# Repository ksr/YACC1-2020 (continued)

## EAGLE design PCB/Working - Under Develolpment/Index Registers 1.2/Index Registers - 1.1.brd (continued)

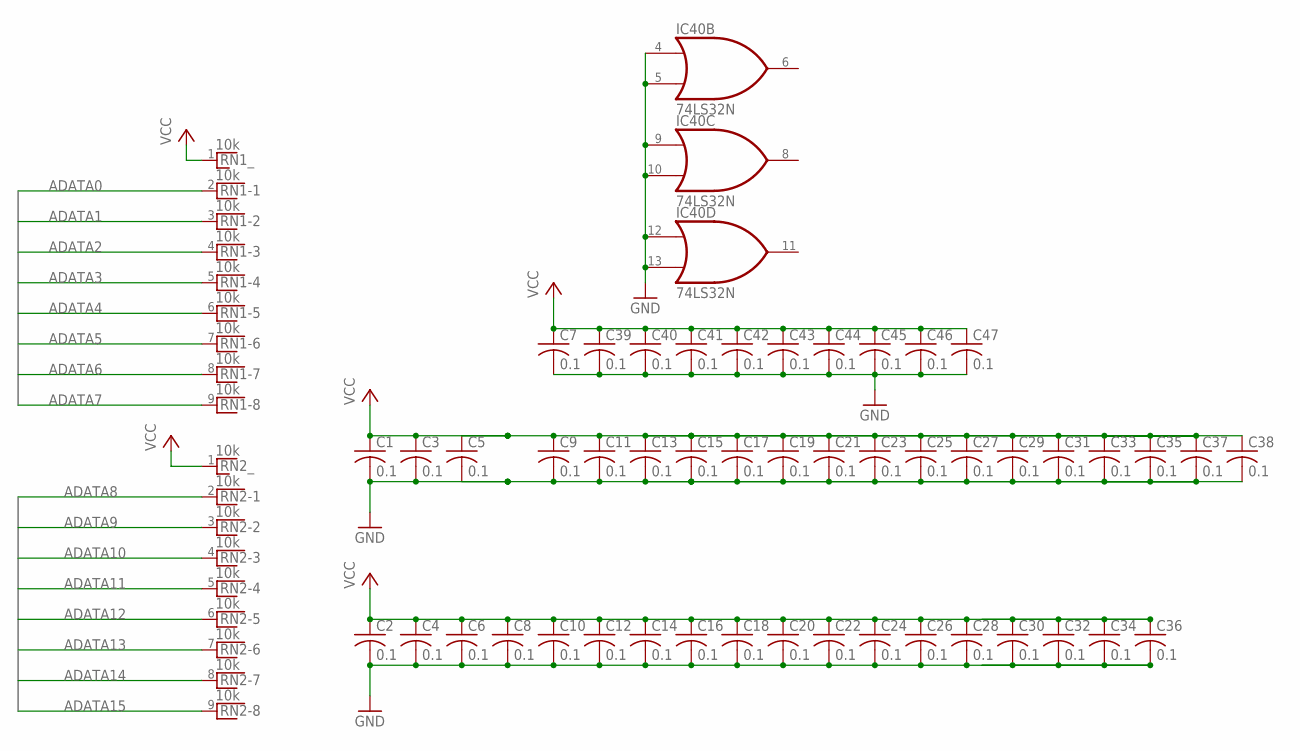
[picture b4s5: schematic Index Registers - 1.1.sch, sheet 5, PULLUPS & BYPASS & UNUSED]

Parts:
C1, C2, C3, C4, C5, C6, C7, C8, C9, C10, C11, C12, C13, C14, C15, C16, C17, C18, C19, C20, C21, C22, C23, C24, C25, C26, C27, C28, C29, C30, C31, C32, C33, C34, C35, C36, C37, C38, C39, C40, C41, C42, C43, C44, C45, C46, C47: 0.1; C025-040X050
IC40: 74LS32N; DIL14
RN1, RN2: 10k; RN-9

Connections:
ADATA0: RN1.2; also elsewhere on the board
ADATA1: RN1.3; also elsewhere on the board
ADATA2: RN1.4; also elsewhere on the board
ADATA3: RN1.5; also elsewhere on the board
ADATA4: RN1.6; also elsewhere on the board
ADATA5: RN1.7; also elsewhere on the board
ADATA6: RN1.8; also elsewhere on the board
ADATA7: RN1.9; also elsewhere on the board
ADATA8: RN2.2; also elsewhere on the board
ADATA9: RN2.3; also elsewhere on the board
ADATA10: RN2.4; also elsewhere on the board
ADATA11: RN2.5; also elsewhere on the board
ADATA12: RN2.6; also elsewhere on the board
ADATA13: RN2.7; also elsewhere on the board
ADATA14: RN2.8; also elsewhere on the board
ADATA15: RN2.9; also elsewhere on the board
GND: C1.2, C2.2, C3.2, C4.2, C5.2, C6.2, C7.2, C8.2, C9.2, C10.2, C11.2, C12.2, C13.2, C14.2, C15.2, C16.2, C17.2, C18.2, C19.2, C20.2, C21.2, C22.2, C23.2, C24.2, C25.2, C26.2, C27.2, C28.2, C29.2, C30.2, C31.2, C32.2, C33.2, C34.2, C35.2, C36.2, C37.2, C38.2, C39.2, C40.2, C41.2, C42.2, C43.2, C44.2, C45.2, C46.2, C47.2, IC40.4 (I0), IC40.5 (I1), IC40.7 (GND), IC40.9 (I0), IC40.10 (I1), IC40.12 (I0), IC40.13 (I1); also elsewhere on the board
VCC: C1.1, C2.1, C3.1, C4.1, C5.1, C6.1, C7.1, C8.1, C9.1, C10.1, C11.1, C12.1, C13.1, C14.1, C15.1, C16.1, C17.1, C18.1, C19.1, C20.1, C21.1, C22.1, C23.1, C24.1, C25.1, C26.1, C27.1, C28.1, C29.1, C30.1, C31.1, C32.1, C33.1, C34.1, C35.1, C36.1, C37.1, C38.1, C39.1, C40.1, C41.1, C42.1, C43.1, C44.1, C45.1, C46.1, C47.1, IC40.14 (VCC), RN1.1, RN2.1; also elsewhere on the board

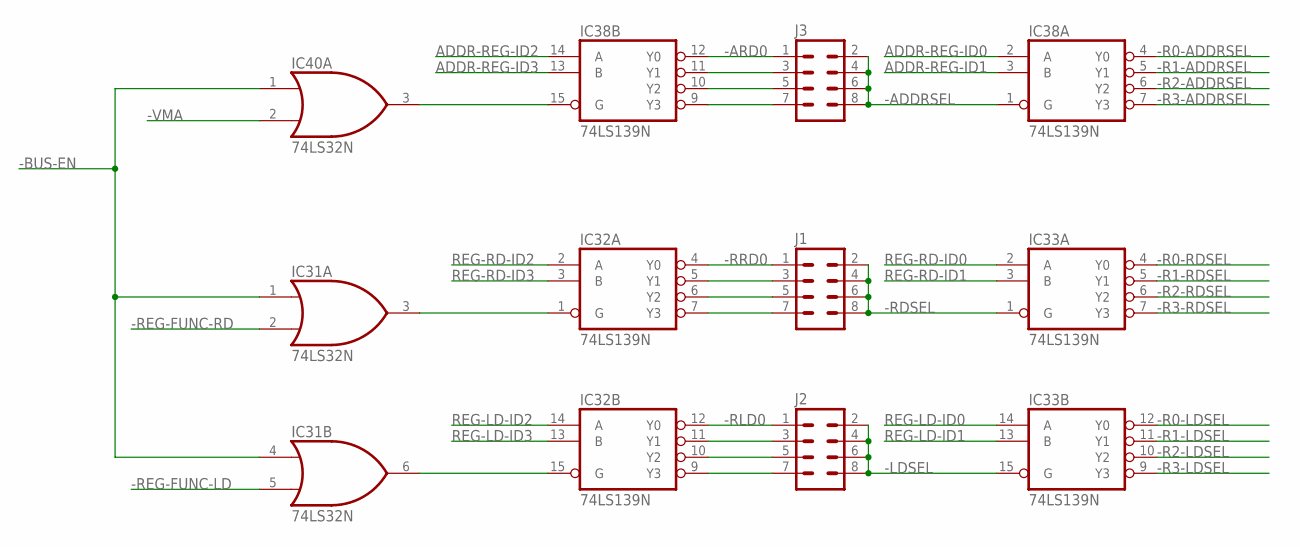
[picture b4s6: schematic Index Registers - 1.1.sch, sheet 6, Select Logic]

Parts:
IC31, IC40: 74LS32N; DIL14
IC32, IC33, IC38: 74LS139N; DIL16
J1, J2, J3: M04X2; 2X4

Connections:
-ADDRSEL: IC38.1 (G), J3.2, J3.4, J3.6, J3.8
-ARD0: IC38.12 (Y0), J3.1
-BUS-EN: IC31.1 (I0), IC31.4 (I0), IC40.1 (I0); also elsewhere on the board
-LDSEL: IC33.15 (G), J2.2, J2.4, J2.6, J2.8; also elsewhere on the board
-R0-ADDRSEL: IC38.4 (Y0); also elsewhere on the board
-R0-LDSEL: IC33.12 (Y0); also elsewhere on the board
-R0-RDSEL: IC33.4 (Y0); also elsewhere on the board
-R1-ADDRSEL: IC38.5 (Y1); also elsewhere on the board
-R1-LDSEL: IC33.11 (Y1); also elsewhere on the board
-R1-RDSEL: IC33.5 (Y1); also elsewhere on the board
-R2-ADDRSEL: IC38.6 (Y2); also elsewhere on the board
-R2-LDSEL: IC33.10 (Y2); also elsewhere on the board
-R2-RDSEL: IC33.6 (Y2); also elsewhere on the board
-R3-ADDRSEL: IC38.7 (Y3); also elsewhere on the board
-R3-LDSEL: IC33.9 (Y3); also elsewhere on the board
-R3-RDSEL: IC33.7 (Y3); also elsewhere on the board
-RDSEL: IC33.1 (G), J1.2, J1.4, J1.6, J1.8; also elsewhere on the board
-REG-FUNC-LD: IC31.5 (I1); also elsewhere on the board
-REG-FUNC-RD: IC31.2 (I1); also elsewhere on the board
-RLD0: IC32.12 (Y0), J2.1
-RRD0: IC32.4 (Y0), J1.1
-VMA: IC40.2 (I1); also elsewhere on the board
ADDR-REG-ID0: IC38.2 (A); also elsewhere on the board
ADDR-REG-ID1: IC38.3 (B); also elsewhere on the board
ADDR-REG-ID2: IC38.14 (A); also elsewhere on the board
ADDR-REG-ID3: IC38.13 (B); also elsewhere on the board
GND: IC31.7 (GND), IC32.8 (GND), IC33.8 (GND), IC38.8 (GND), IC40.7 (GND); also elsewhere on the board
unnamed: IC31.3 (O), IC32.1 (G)
unnamed: IC31.6 (O), IC32.15 (G)
unnamed: IC32.5 (Y1), J1.3
unnamed: IC38.15 (G), IC40.3 (O)
unnamed: IC32.6 (Y2), J1.5
unnamed: IC32.7 (Y3), J1.7
unnamed: IC32.11 (Y1), J2.3
unnamed: IC32.10 (Y2), J2.5
unnamed: IC32.9 (Y3), J2.7
unnamed: IC38.11 (Y1), J3.3
unnamed: IC38.10 (Y2), J3.5
unnamed: IC38.9 (Y3), J3.7
REG-LD-ID0: IC33.14 (A); also elsewhere on the board
REG-LD-ID1: IC33.13 (B); also elsewhere on the board
REG-LD-ID2: IC32.14 (A); also elsewhere on the board
REG-LD-ID3: IC32.13 (B); also elsewhere on the board
REG-RD-ID0: IC33.2 (A); also elsewhere on the board
REG-RD-ID1: IC33.3 (B); also elsewhere on the board
REG-RD-ID2: IC32.2 (A); also elsewhere on the board
REG-RD-ID3: IC32.3 (B); also elsewhere on the board
VCC: IC31.14 (VCC), IC32.16 (VCC), IC33.16 (VCC), IC38.16 (VCC), IC40.14 (VCC); also elsewhere on the board

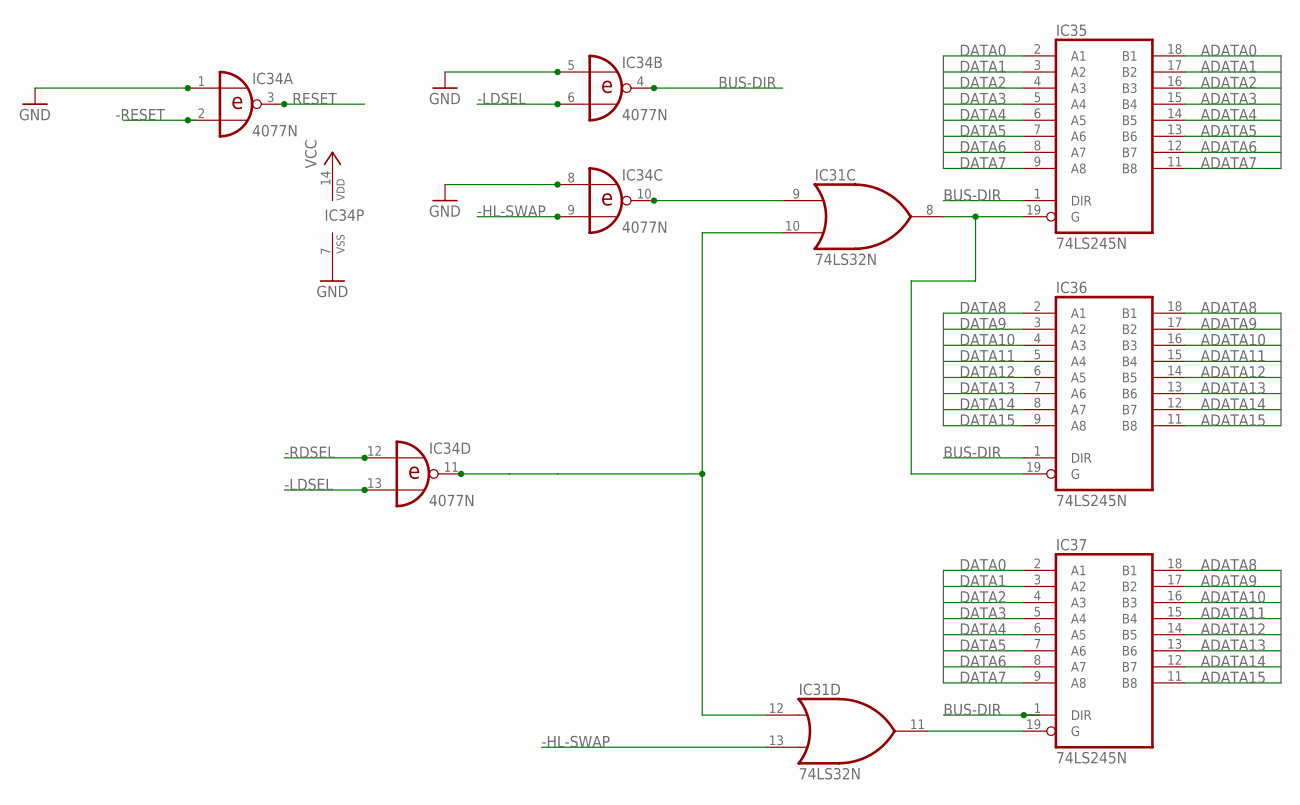
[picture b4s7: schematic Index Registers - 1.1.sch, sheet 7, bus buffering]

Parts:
IC31: 74LS32N; DIL14
IC34: 4077N; DIL14
IC35, IC36, IC37: 74LS245N; DIL20

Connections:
-HL-SWAP: IC31.13 (I1), IC34.9 (I1); also elsewhere on the board
-LDSEL: IC34.6 (I1), IC34.13 (I1); also elsewhere on the board
-RDSEL: IC34.12 (I0); also elsewhere on the board
-RESET: IC34.2 (I1); also elsewhere on the board
ADATA0: IC35.18 (B1); also elsewhere on the board
ADATA1: IC35.17 (B2); also elsewhere on the board
ADATA2: IC35.16 (B3); also elsewhere on the board
ADATA3: IC35.15 (B4); also elsewhere on the board
ADATA4: IC35.14 (B5); also elsewhere on the board
ADATA5: IC35.13 (B6); also elsewhere on the board
ADATA6: IC35.12 (B7); also elsewhere on the board
ADATA7: IC35.11 (B8); also elsewhere on the board
ADATA8: IC36.18 (B1), IC37.18 (B1); also elsewhere on the board
ADATA9: IC36.17 (B2), IC37.17 (B2); also elsewhere on the board
ADATA10: IC36.16 (B3), IC37.16 (B3); also elsewhere on the board
ADATA11: IC36.15 (B4), IC37.15 (B4); also elsewhere on the board
ADATA12: IC36.14 (B5), IC37.14 (B5); also elsewhere on the board
ADATA13: IC36.13 (B6), IC37.13 (B6); also elsewhere on the board
ADATA14: IC36.12 (B7), IC37.12 (B7); also elsewhere on the board
ADATA15: IC36.11 (B8), IC37.11 (B8); also elsewhere on the board
BUS-DIR: IC34.4 (O), IC35.1 (DIR), IC36.1 (DIR), IC37.1 (DIR)
DATA0: IC35.2 (A1), IC37.2 (A1); also elsewhere on the board
DATA1: IC35.3 (A2), IC37.3 (A2); also elsewhere on the board
DATA2: IC35.4 (A3), IC37.4 (A3); also elsewhere on the board
DATA3: IC35.5 (A4), IC37.5 (A4); also elsewhere on the board
DATA4: IC35.6 (A5), IC37.6 (A5); also elsewhere on the board
DATA5: IC35.7 (A6), IC37.7 (A6); also elsewhere on the board
DATA6: IC35.8 (A7), IC37.8 (A7); also elsewhere on the board
DATA7: IC35.9 (A8), IC37.9 (A8); also elsewhere on the board
DATA8: IC36.2 (A1); also elsewhere on the board
DATA9: IC36.3 (A2); also elsewhere on the board
DATA10: IC36.4 (A3); also elsewhere on the board
DATA11: IC36.5 (A4); also elsewhere on the board
DATA12: IC36.6 (A5); also elsewhere on the board
DATA13: IC36.7 (A6); also elsewhere on the board
DATA14: IC36.8 (A7); also elsewhere on the board
DATA15: IC36.9 (A8); also elsewhere on the board
GND: IC31.7 (GND), IC34.1 (I0), IC34.5 (I0), IC34.7 (VSS), IC34.8 (I0), IC35.10 (GND), IC36.10 (GND), IC37.10 (GND); also elsewhere on the board
unnamed: IC31.8 (O), IC35.19 (G), IC36.19 (G)
unnamed: IC31.11 (O), IC37.19 (G)
unnamed: IC31.9 (I0), IC34.10 (O)
unnamed: IC31.10 (I1), IC31.12 (I0), IC34.11 (O)
RESET: IC34.3 (O); also elsewhere on the board
VCC: IC31.14 (VCC), IC34.14 (VDD), IC35.20 (VCC), IC36.20 (VCC), IC37.20 (VCC); also elsewhere on the board

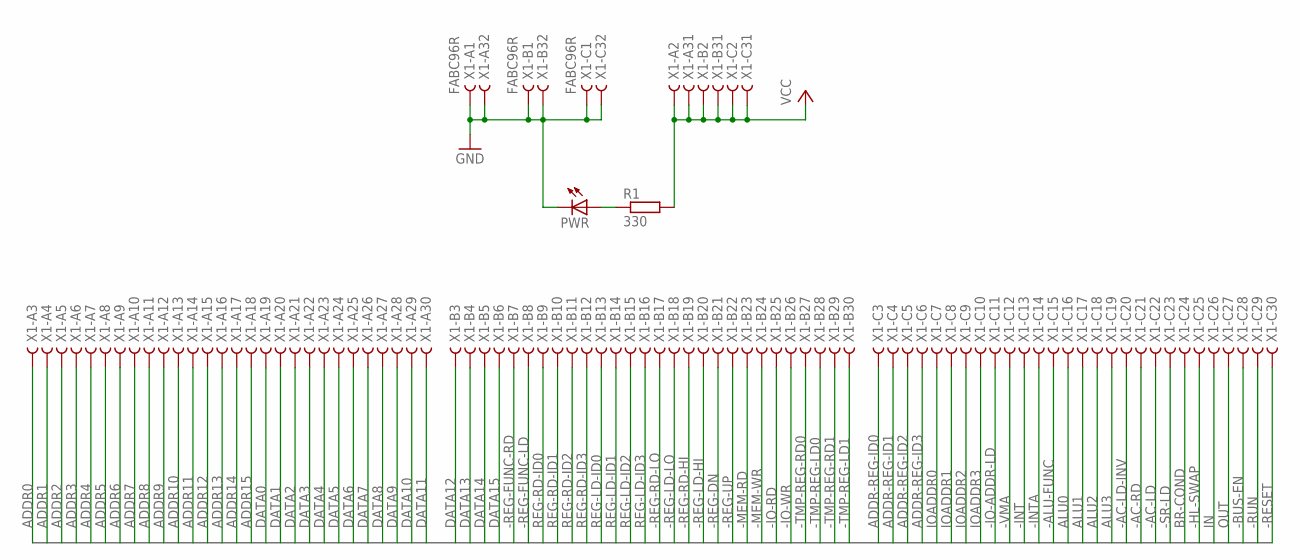
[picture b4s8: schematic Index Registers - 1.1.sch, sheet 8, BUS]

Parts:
PWR: LED5MM
R1: 330; 0207/10
X1: FABC96R

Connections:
-AC-LD: X1.C22
-AC-LD-INV: X1.C20
-AC-RD: X1.C21
-ALU-FUNC: X1.C15
-BUS-EN: X1.C28; also elsewhere on the board
-HL-SWAP: X1.C25; also elsewhere on the board
-INT: X1.C13
-INTA: X1.C14
-IO-ADDR-LD: X1.C11
-IO-RD: X1.B25
-IO-WR: X1.B26
-MEM-RD: X1.B23
-MEM-WR: X1.B24
-REG-DN: X1.B21; also elsewhere on the board
-REG-FUNC-LD: X1.B8; also elsewhere on the board
-REG-FUNC-RD: X1.B7; also elsewhere on the board
-REG-LD-HI: X1.B20; also elsewhere on the board
-REG-LD-LO: X1.B18; also elsewhere on the board
-REG-RD-HI: X1.B19; also elsewhere on the board
-REG-RD-LO: X1.B17; also elsewhere on the board
-REG-UP: X1.B22; also elsewhere on the board
-RESET: X1.C30; also elsewhere on the board
-RUN: X1.C29
-SR-LD: X1.C23
-TMP-REG-LD0: X1.B28
-TMP-REG-LD1: X1.B30
-TMP-REG-RD0: X1.B27
-TMP-REG-RD1: X1.B29
-VMA: X1.C12; also elsewhere on the board
ADDR0: X1.A3; also elsewhere on the board
ADDR1: X1.A4; also elsewhere on the board
ADDR2: X1.A5; also elsewhere on the board
ADDR3: X1.A6; also elsewhere on the board
ADDR4: X1.A7; also elsewhere on the board
ADDR5: X1.A8; also elsewhere on the board
ADDR6: X1.A9; also elsewhere on the board
ADDR7: X1.A10; also elsewhere on the board
ADDR8: X1.A11; also elsewhere on the board
ADDR9: X1.A12; also elsewhere on the board
ADDR10: X1.A13; also elsewhere on the board
ADDR11: X1.A14; also elsewhere on the board
ADDR12: X1.A15; also elsewhere on the board
ADDR13: X1.A16; also elsewhere on the board
ADDR14: X1.A17; also elsewhere on the board
ADDR15: X1.A18; also elsewhere on the board
ADDR-REG-ID0: X1.C3; also elsewhere on the board
ADDR-REG-ID1: X1.C4; also elsewhere on the board
ADDR-REG-ID2: X1.C5; also elsewhere on the board
ADDR-REG-ID3: X1.C6; also elsewhere on the board
ALU0: X1.C16
ALU1: X1.C17
ALU2: X1.C18
ALU3: X1.C19
BR-COND: X1.C24
DATA0: X1.A19; also elsewhere on the board
DATA1: X1.A20; also elsewhere on the board
DATA2: X1.A21; also elsewhere on the board
DATA3: X1.A22; also elsewhere on the board
DATA4: X1.A23; also elsewhere on the board
DATA5: X1.A24; also elsewhere on the board
DATA6: X1.A25; also elsewhere on the board
DATA7: X1.A26; also elsewhere on the board
DATA8: X1.A27; also elsewhere on the board
DATA9: X1.A28; also elsewhere on the board
DATA10: X1.A29; also elsewhere on the board
DATA11: X1.A30; also elsewhere on the board
DATA12: X1.B3; also elsewhere on the board
DATA13: X1.B4; also elsewhere on the board
DATA14: X1.B5; also elsewhere on the board
DATA15: X1.B6; also elsewhere on the board
GND: PWR.K (C), X1.A1, X1.A32, X1.B1, X1.B32, X1.C1, X1.C32; also elsewhere on the board
IN: X1.C26
IOADDR0: X1.C7
IOADDR1: X1.C8
IOADDR2: X1.C9
IOADDR3: X1.C10
unnamed: PWR.A, R1.1
OUT: X1.C27
REG-LD-ID0: X1.B13; also elsewhere on the board
REG-LD-ID1: X1.B14; also elsewhere on the board
REG-LD-ID2: X1.B15; also elsewhere on the board
REG-LD-ID3: X1.B16; also elsewhere on the board
REG-RD-ID0: X1.B9; also elsewhere on the board
REG-RD-ID1: X1.B10; also elsewhere on the board
REG-RD-ID2: X1.B11; also elsewhere on the board
REG-RD-ID3: X1.B12; also elsewhere on the board
VCC: R1.2, X1.A2, X1.A31, X1.B2, X1.B31, X1.C2, X1.C31; also elsewhere on the board

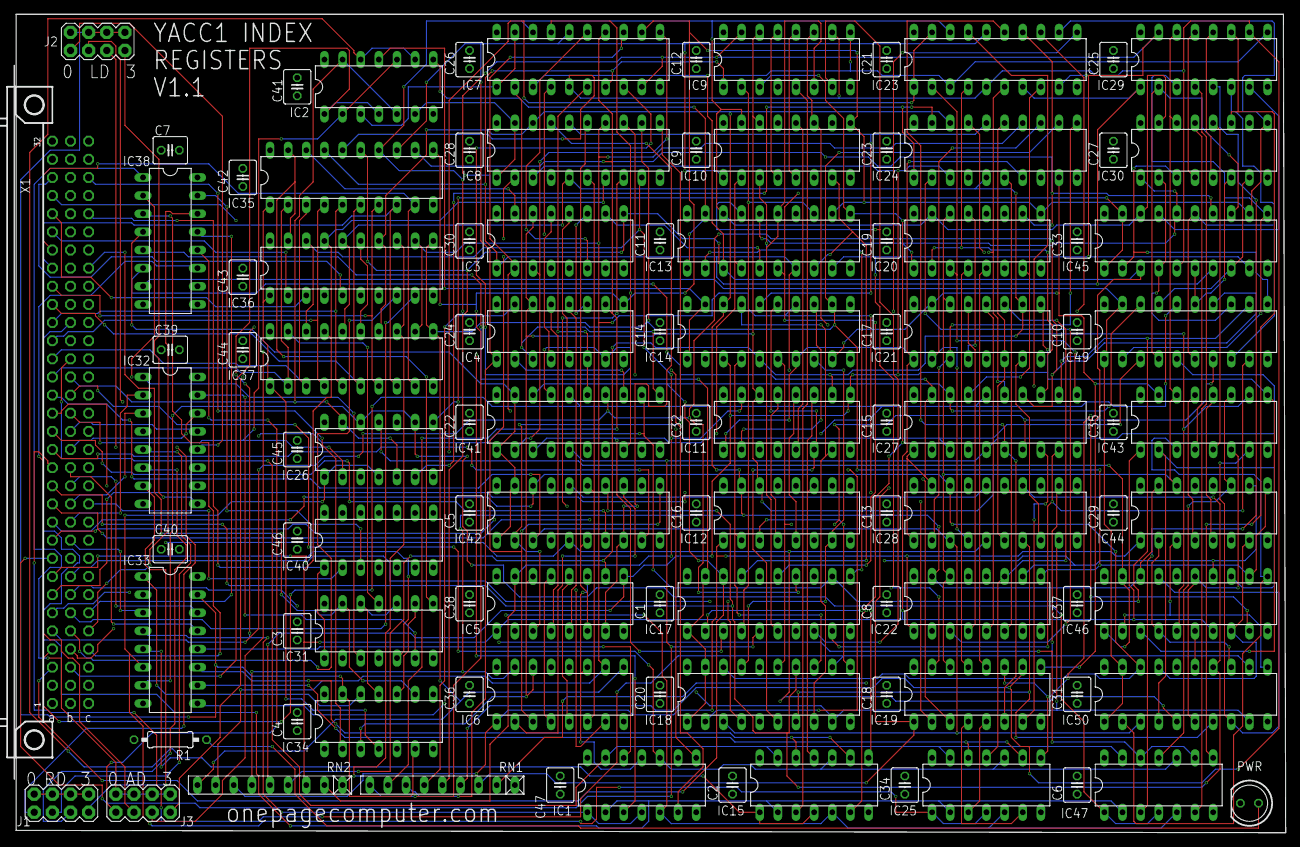
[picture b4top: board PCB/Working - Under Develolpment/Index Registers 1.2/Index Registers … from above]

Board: 4 copper layers, 177.8 x 114.6 mm, 102 parts (0 on the bottom side), 223 nets.

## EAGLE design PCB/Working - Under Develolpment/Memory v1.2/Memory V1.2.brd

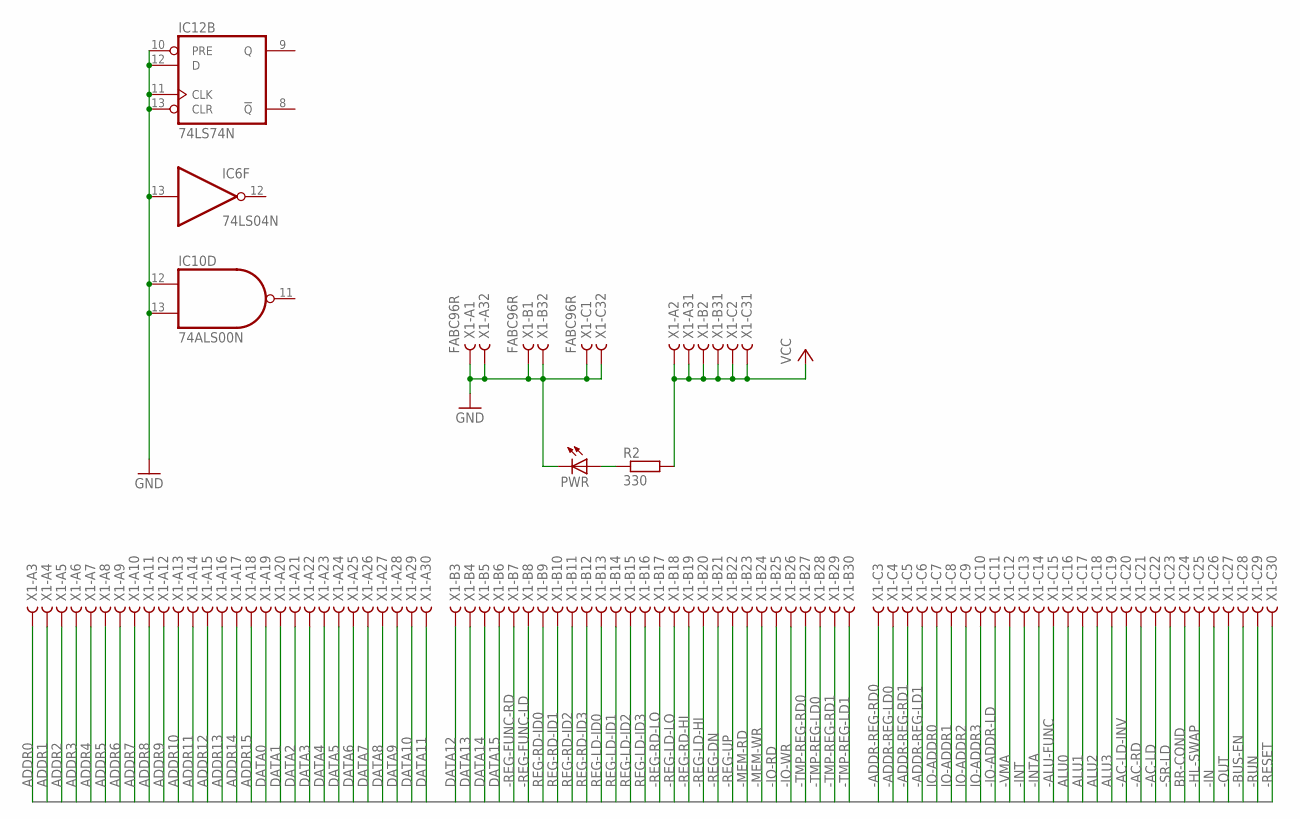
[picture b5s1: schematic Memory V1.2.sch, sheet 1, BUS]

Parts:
IC6: 74LS04N; DIL14
IC10: 74ALS00N; DIL14
IC12: 74LS74N; DIL14
PWR: LED5MM
R2: 330; 0207/10
X1: FABC96R

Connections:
-AC-LD: X1.C22
-AC-LD-INV: X1.C20
-AC-RD: X1.C21
-ADDR-REG-LD0: X1.C4
-ADDR-REG-LD1: X1.C6
-ADDR-REG-RD0: X1.C3
-ADDR-REG-RD1: X1.C5
-ALU-FUNC: X1.C15
-BUS-EN: X1.C28
-HL-SWAP: X1.C25
-IN: X1.C26
-INT: X1.C13
-INTA: X1.C14
-IO-ADDR-LD: X1.C11
-IO-RD: X1.B25
-IO-WR: X1.B26
-MEM-RD: X1.B23; also elsewhere on the board
-MEM-WR: X1.B24; also elsewhere on the board
-OUT: X1.C27
-REG-DN: X1.B21
-REG-FUNC-LD: X1.B8
-REG-FUNC-RD: X1.B7
-REG-LD-HI: X1.B20
-REG-LD-LO: X1.B18
-REG-RD-HI: X1.B19
-REG-RD-LO: X1.B17
-REG-UP: X1.B22
-RESET: X1.C30; also elsewhere on the board
-RUN: X1.C29
-SR-LD: X1.C23
-TMP-REG-LD0: X1.B28
-TMP-REG-LD1: X1.B30
-TMP-REG-RD0: X1.B27
-TMP-REG-RD1: X1.B29
-VMA: X1.C12; also elsewhere on the board
ADDR0: X1.A3; also elsewhere on the board
ADDR1: X1.A4; also elsewhere on the board
ADDR2: X1.A5; also elsewhere on the board
ADDR3: X1.A6; also elsewhere on the board
ADDR4: X1.A7; also elsewhere on the board
ADDR5: X1.A8; also elsewhere on the board
ADDR6: X1.A9; also elsewhere on the board
ADDR7: X1.A10; also elsewhere on the board
ADDR8: X1.A11; also elsewhere on the board
ADDR9: X1.A12; also elsewhere on the board
ADDR10: X1.A13; also elsewhere on the board
ADDR11: X1.A14; also elsewhere on the board
ADDR12: X1.A15; also elsewhere on the board
ADDR13: X1.A16; also elsewhere on the board
ADDR14: X1.A17; also elsewhere on the board
ADDR15: X1.A18; also elsewhere on the board
ALU0: X1.C16
ALU1: X1.C17
ALU2: X1.C18
ALU3: X1.C19
BR-COND: X1.C24
DATA0: X1.A19; also elsewhere on the board
DATA1: X1.A20; also elsewhere on the board
DATA2: X1.A21; also elsewhere on the board
DATA3: X1.A22; also elsewhere on the board
DATA4: X1.A23; also elsewhere on the board
DATA5: X1.A24; also elsewhere on the board
DATA6: X1.A25; also elsewhere on the board
DATA7: X1.A26; also elsewhere on the board
DATA8: X1.A27
DATA9: X1.A28
DATA10: X1.A29
DATA11: X1.A30
DATA12: X1.B3
DATA13: X1.B4
DATA14: X1.B5
DATA15: X1.B6
GND: IC6.7 (GND), IC6.13 (I), IC10.7 (GND), IC10.12 (I0), IC10.13 (I1), IC12.7 (GND), IC12.10 (PRE), IC12.11 (CLK), IC12.12 (D), IC12.13 (CLR), PWR.K (C), X1.A1, X1.A32, X1.B1, X1.B32, X1.C1, X1.C32; also elsewhere on the board
IO-ADDR0: X1.C7
IO-ADDR1: X1.C8
IO-ADDR2: X1.C9
IO-ADDR3: X1.C10
unnamed: PWR.A, R2.1
REG-LD-ID0: X1.B13
REG-LD-ID1: X1.B14
REG-LD-ID2: X1.B15
REG-LD-ID3: X1.B16
REG-RD-ID0: X1.B9
REG-RD-ID1: X1.B10
REG-RD-ID2: X1.B11
REG-RD-ID3: X1.B12
VCC: IC6.14 (VCC), IC10.14 (VCC), IC12.14 (VCC), R2.2, X1.A2, X1.A31, X1.B2, X1.B31, X1.C2, X1.C31; also elsewhere on the board

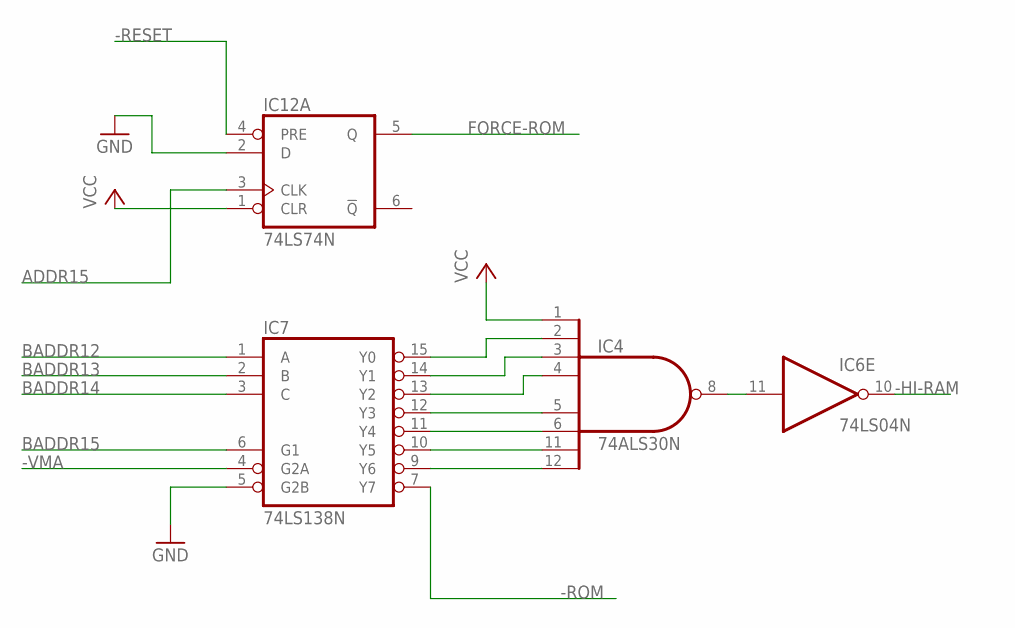
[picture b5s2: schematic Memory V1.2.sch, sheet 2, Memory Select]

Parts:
IC4: 74ALS30N; DIL14
IC6: 74LS04N; DIL14
IC7: 74LS138N; DIL16
IC12: 74LS74N; DIL14

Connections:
-HI-RAM: IC6.10 (O); also elsewhere on the board
-RESET: IC12.4 (PRE); also elsewhere on the board
-ROM: IC7.7 (Y7); also elsewhere on the board
-VMA: IC7.4 (G2A); also elsewhere on the board
ADDR15: IC12.3 (CLK); also elsewhere on the board
BADDR12: IC7.1 (A); also elsewhere on the board
BADDR13: IC7.2 (B); also elsewhere on the board
BADDR14: IC7.3 (C); also elsewhere on the board
BADDR15: IC7.6 (G1); also elsewhere on the board
FORCE-ROM: IC12.5 (Q); also elsewhere on the board
GND: IC4.7 (GND), IC6.7 (GND), IC7.5 (G2B), IC7.8 (GND), IC12.2 (D), IC12.7 (GND); also elsewhere on the board
unnamed: IC4.12 (I7), IC7.9 (Y6)
unnamed: IC4.11 (I6), IC7.10 (Y5)
unnamed: IC4.6 (I5), IC7.11 (Y4)
unnamed: IC4.5 (I4), IC7.12 (Y3)
unnamed: IC4.4 (I3), IC7.13 (Y2)
unnamed: IC4.3 (I2), IC7.14 (Y1)
unnamed: IC4.2 (I1), IC7.15 (Y0)
unnamed: IC4.8 (O), IC6.11 (I)
VCC: IC4.1 (I0), IC4.14 (VCC), IC6.14 (VCC), IC7.16 (VCC), IC12.1 (CLR), IC12.14 (VCC); also elsewhere on the board

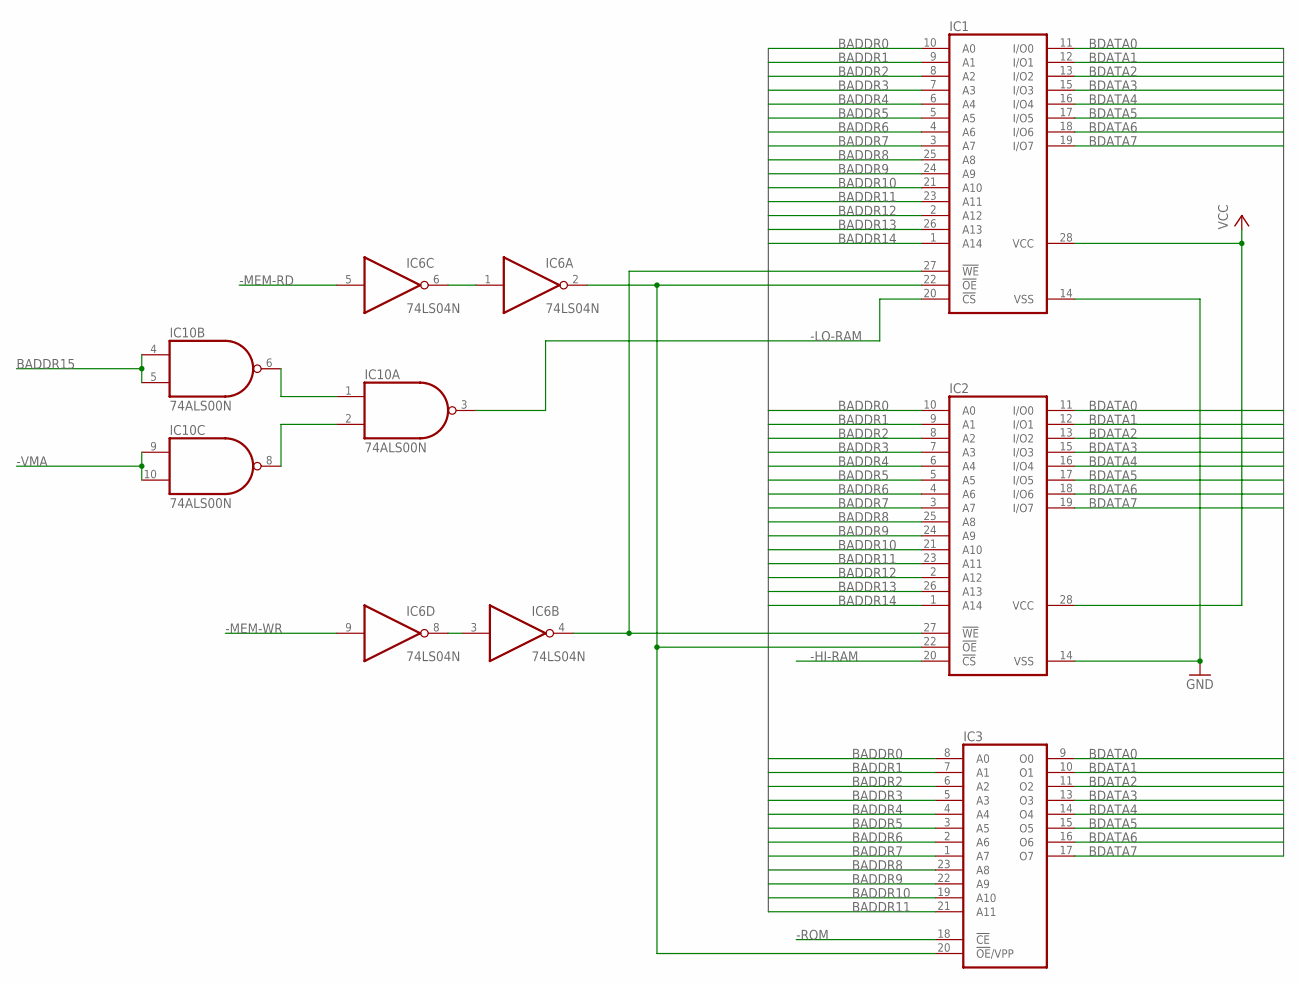
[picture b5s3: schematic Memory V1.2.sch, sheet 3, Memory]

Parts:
IC1, IC2: 62256P; DIL28-6
IC3: 2732; DIL24
IC6: 74LS04N; DIL14
IC10: 74ALS00N; DIL14

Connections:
-HI-RAM: IC2.20 (!CS); also elsewhere on the board
-LO-RAM: IC1.20 (!CS), IC10.3 (O)
-MEM-RD: IC6.5 (I); also elsewhere on the board
-MEM-WR: IC6.9 (I); also elsewhere on the board
-ROM: IC3.18 (!CE); also elsewhere on the board
-VMA: IC10.9 (I0), IC10.10 (I1); also elsewhere on the board
BADDR0: IC1.10 (A0), IC2.10 (A0), IC3.8 (A0); also elsewhere on the board
BADDR1: IC1.9 (A1), IC2.9 (A1), IC3.7 (A1); also elsewhere on the board
BADDR2: IC1.8 (A2), IC2.8 (A2), IC3.6 (A2); also elsewhere on the board
BADDR3: IC1.7 (A3), IC2.7 (A3), IC3.5 (A3); also elsewhere on the board
BADDR4: IC1.6 (A4), IC2.6 (A4), IC3.4 (A4); also elsewhere on the board
BADDR5: IC1.5 (A5), IC2.5 (A5), IC3.3 (A5); also elsewhere on the board
BADDR6: IC1.4 (A6), IC2.4 (A6), IC3.2 (A6); also elsewhere on the board
BADDR7: IC1.3 (A7), IC2.3 (A7), IC3.1 (A7); also elsewhere on the board
BADDR8: IC1.25 (A8), IC2.25 (A8), IC3.23 (A8); also elsewhere on the board
BADDR9: IC1.24 (A9), IC2.24 (A9), IC3.22 (A9); also elsewhere on the board
BADDR10: IC1.21 (A10), IC2.21 (A10), IC3.19 (A10); also elsewhere on the board
BADDR11: IC1.23 (A11), IC2.23 (A11), IC3.21 (A11); also elsewhere on the board
BADDR12: IC1.2 (A12), IC2.2 (A12); also elsewhere on the board
BADDR13: IC1.26 (A13), IC2.26 (A13); also elsewhere on the board
BADDR14: IC1.1 (A14), IC2.1 (A14); also elsewhere on the board
BADDR15: IC10.4 (I0), IC10.5 (I1); also elsewhere on the board
BDATA0: IC1.11 (I/O0), IC2.11 (I/O0), IC3.9 (O0); also elsewhere on the board
BDATA1: IC1.12 (I/O1), IC2.12 (I/O1), IC3.10 (O1); also elsewhere on the board
BDATA2: IC1.13 (I/O2), IC2.13 (I/O2), IC3.11 (O2); also elsewhere on the board
BDATA3: IC1.15 (I/O3), IC2.15 (I/O3), IC3.13 (O3); also elsewhere on the board
BDATA4: IC1.16 (I/O4), IC2.16 (I/O4), IC3.14 (O4); also elsewhere on the board
BDATA5: IC1.17 (I/O5), IC2.17 (I/O5), IC3.15 (O5); also elsewhere on the board
BDATA6: IC1.18 (I/O6), IC2.18 (I/O6), IC3.16 (O6); also elsewhere on the board
BDATA7: IC1.19 (I/O7), IC2.19 (I/O7), IC3.17 (O7); also elsewhere on the board
GND: IC1.14 (VSS), IC2.14 (VSS), IC3.12 (GND), IC6.7 (GND), IC10.7 (GND); also elsewhere on the board
MEM-RD: IC6.1 (I), IC6.6 (O)
unnamed: IC6.3 (I), IC6.8 (O)
unnamed: IC1.22 (!OE), IC2.22 (!OE), IC3.20 (!OE!/VPP), IC6.2 (O)
unnamed: IC1.27 (!WE), IC2.27 (!WE), IC6.4 (O)
unnamed: IC10.2 (I1), IC10.8 (O)
unnamed: IC10.1 (I0), IC10.6 (O)
VCC: IC1.28 (VCC), IC2.28 (VCC), IC3.24 (VCC), IC6.14 (VCC), IC10.14 (VCC); also elsewhere on the board

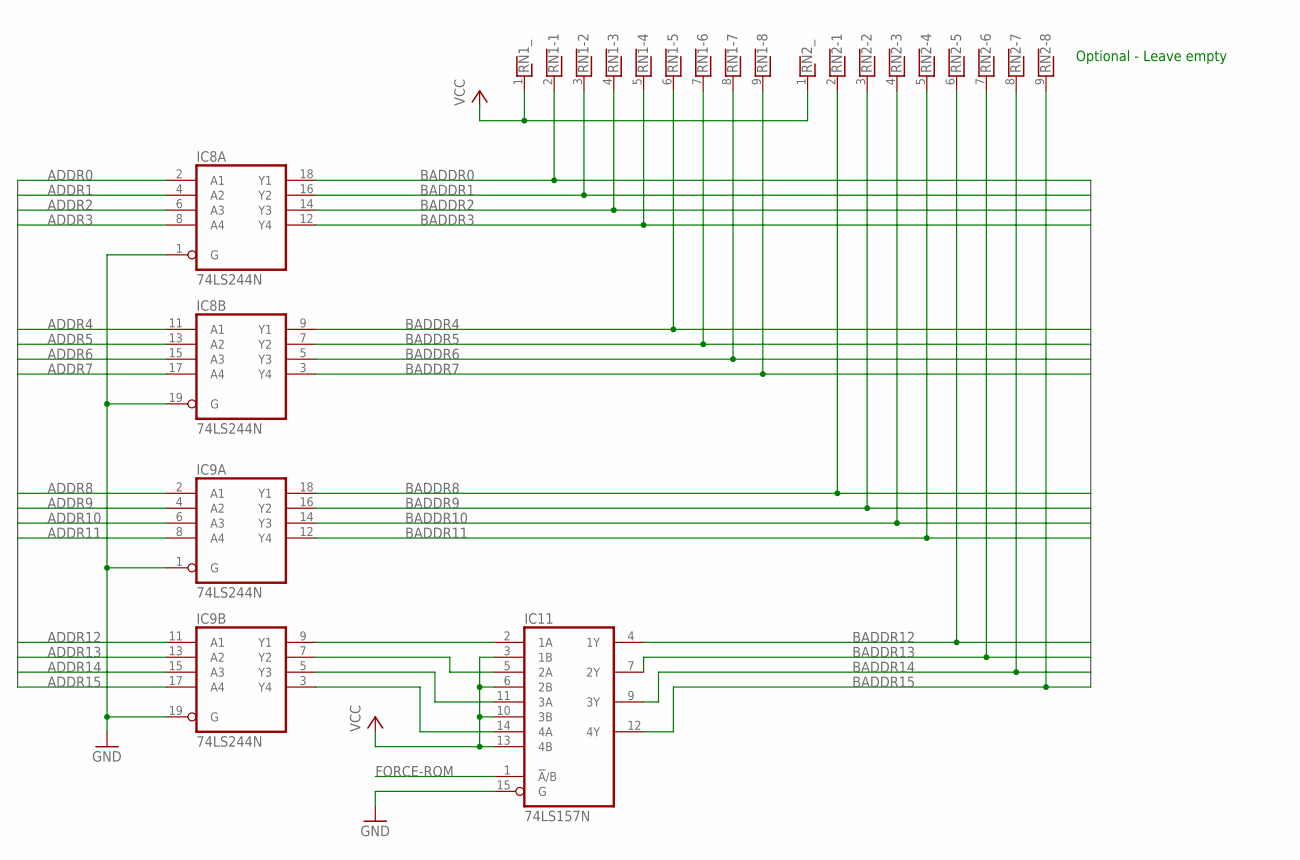
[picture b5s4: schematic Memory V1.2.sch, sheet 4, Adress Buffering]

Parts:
IC8, IC9: 74LS244N; DIL20
IC11: 74LS157N; DIL16
RN1, RN2: RNX8; RN-9

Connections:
ADDR0: IC8.2 (A1); also elsewhere on the board
ADDR1: IC8.4 (A2); also elsewhere on the board
ADDR2: IC8.6 (A3); also elsewhere on the board
ADDR3: IC8.8 (A4); also elsewhere on the board
ADDR4: IC8.11 (A1); also elsewhere on the board
ADDR5: IC8.13 (A2); also elsewhere on the board
ADDR6: IC8.15 (A3); also elsewhere on the board
ADDR7: IC8.17 (A4); also elsewhere on the board
ADDR8: IC9.2 (A1); also elsewhere on the board
ADDR9: IC9.4 (A2); also elsewhere on the board
ADDR10: IC9.6 (A3); also elsewhere on the board
ADDR11: IC9.8 (A4); also elsewhere on the board
ADDR12: IC9.11 (A1); also elsewhere on the board
ADDR13: IC9.13 (A2); also elsewhere on the board
ADDR14: IC9.15 (A3); also elsewhere on the board
ADDR15: IC9.17 (A4); also elsewhere on the board
BADDR0: IC8.18 (Y1), RN1.2; also elsewhere on the board
BADDR1: IC8.16 (Y2), RN1.3; also elsewhere on the board
BADDR2: IC8.14 (Y3), RN1.4; also elsewhere on the board
BADDR3: IC8.12 (Y4), RN1.5; also elsewhere on the board
BADDR4: IC8.9 (Y1), RN1.6; also elsewhere on the board
BADDR5: IC8.7 (Y2), RN1.7; also elsewhere on the board
BADDR6: IC8.5 (Y3), RN1.8; also elsewhere on the board
BADDR7: IC8.3 (Y4), RN1.9; also elsewhere on the board
BADDR8: IC9.18 (Y1), RN2.2; also elsewhere on the board
BADDR9: IC9.16 (Y2), RN2.3; also elsewhere on the board
BADDR10: IC9.14 (Y3), RN2.4; also elsewhere on the board
BADDR11: IC9.12 (Y4), RN2.5; also elsewhere on the board
BADDR12: IC11.4 (1Y), RN2.6; also elsewhere on the board
BADDR13: IC11.7 (2Y), RN2.7; also elsewhere on the board
BADDR14: IC11.9 (3Y), RN2.8; also elsewhere on the board
BADDR15: IC11.12 (4Y), RN2.9; also elsewhere on the board
FORCE-ROM: IC11.1 (!A!/B); also elsewhere on the board
GND: IC8.1 (G), IC8.10 (GND), IC8.19 (G), IC9.1 (G), IC9.10 (GND), IC9.19 (G), IC11.8 (GND), IC11.15 (G); also elsewhere on the board
unnamed: IC9.9 (Y1), IC11.2 (1A)
unnamed: IC9.7 (Y2), IC11.5 (2A)
unnamed: IC9.5 (Y3), IC11.11 (3A)
unnamed: IC9.3 (Y4), IC11.14 (4A)
VCC: IC8.20 (VCC), IC9.20 (VCC), IC11.3 (1B), IC11.6 (2B), IC11.10 (3B), IC11.13 (4B), IC11.16 (VCC), RN1.1, RN2.1; also elsewhere on the board

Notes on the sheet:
Optional - Leave empty

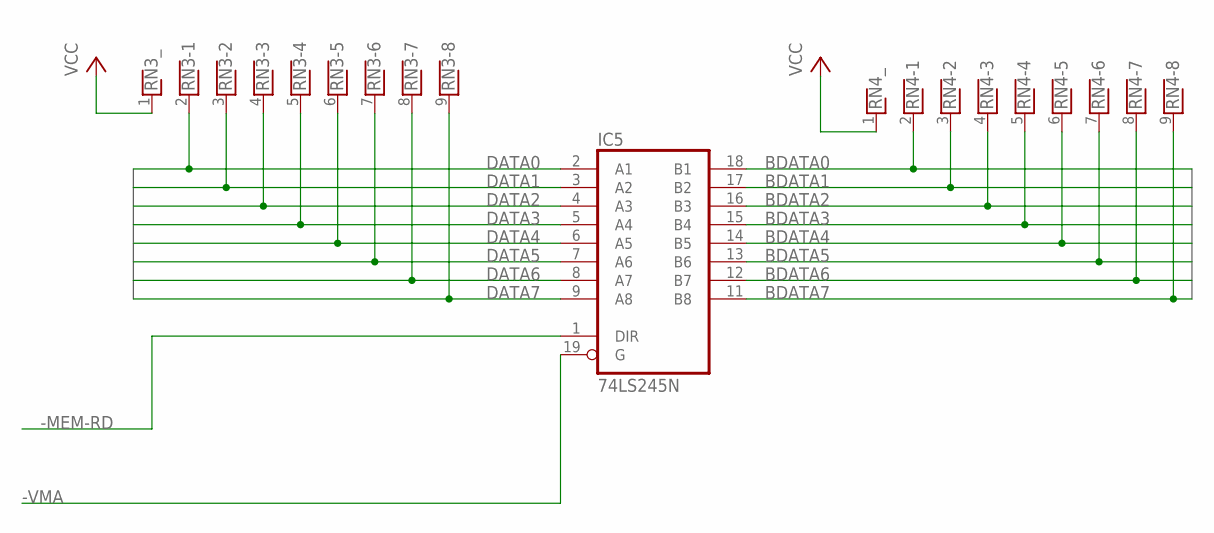
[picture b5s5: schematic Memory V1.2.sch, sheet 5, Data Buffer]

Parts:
IC5: 74LS245N; DIL20
RN3, RN4: RNX8; RN-9

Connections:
-MEM-RD: IC5.1 (DIR); also elsewhere on the board
-VMA: IC5.19 (G); also elsewhere on the board
BDATA0: IC5.18 (B1), RN4.2; also elsewhere on the board
BDATA1: IC5.17 (B2), RN4.3; also elsewhere on the board
BDATA2: IC5.16 (B3), RN4.4; also elsewhere on the board
BDATA3: IC5.15 (B4), RN4.5; also elsewhere on the board
BDATA4: IC5.14 (B5), RN4.6; also elsewhere on the board
BDATA5: IC5.13 (B6), RN4.7; also elsewhere on the board
BDATA6: IC5.12 (B7), RN4.8; also elsewhere on the board
BDATA7: IC5.11 (B8), RN4.9; also elsewhere on the board
DATA0: IC5.2 (A1), RN3.2; also elsewhere on the board
DATA1: IC5.3 (A2), RN3.3; also elsewhere on the board
DATA2: IC5.4 (A3), RN3.4; also elsewhere on the board
DATA3: IC5.5 (A4), RN3.5; also elsewhere on the board
DATA4: IC5.6 (A5), RN3.6; also elsewhere on the board
DATA5: IC5.7 (A6), RN3.7; also elsewhere on the board
DATA6: IC5.8 (A7), RN3.8; also elsewhere on the board
DATA7: IC5.9 (A8), RN3.9; also elsewhere on the board
GND: IC5.10 (GND); also elsewhere on the board
VCC: IC5.20 (VCC), RN3.1, RN4.1; also elsewhere on the board
